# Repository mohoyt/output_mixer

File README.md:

# Output mixer for Eurorack

Inspired by the mixer in the Erica Synths x mki.edu line (but with added channels and SMD components)

## Features
- Eurorack format (3U panel height = 133.4mm)
- 8HP width (about 40mm)
- 4 inputs with pan (L-R) and level adjustable
- 2 outputs, line out and headphone out
- Mostly SMD with a couple through hole parts

## Issues
- [x] Pan is reversed
- [x] Not enough space for 1W 47R resistor
- [x] BD139/140 overheating

All addressed in current version (v1.1). The overheating was a result of poor quality BD139 and BD140 that I had sourced.

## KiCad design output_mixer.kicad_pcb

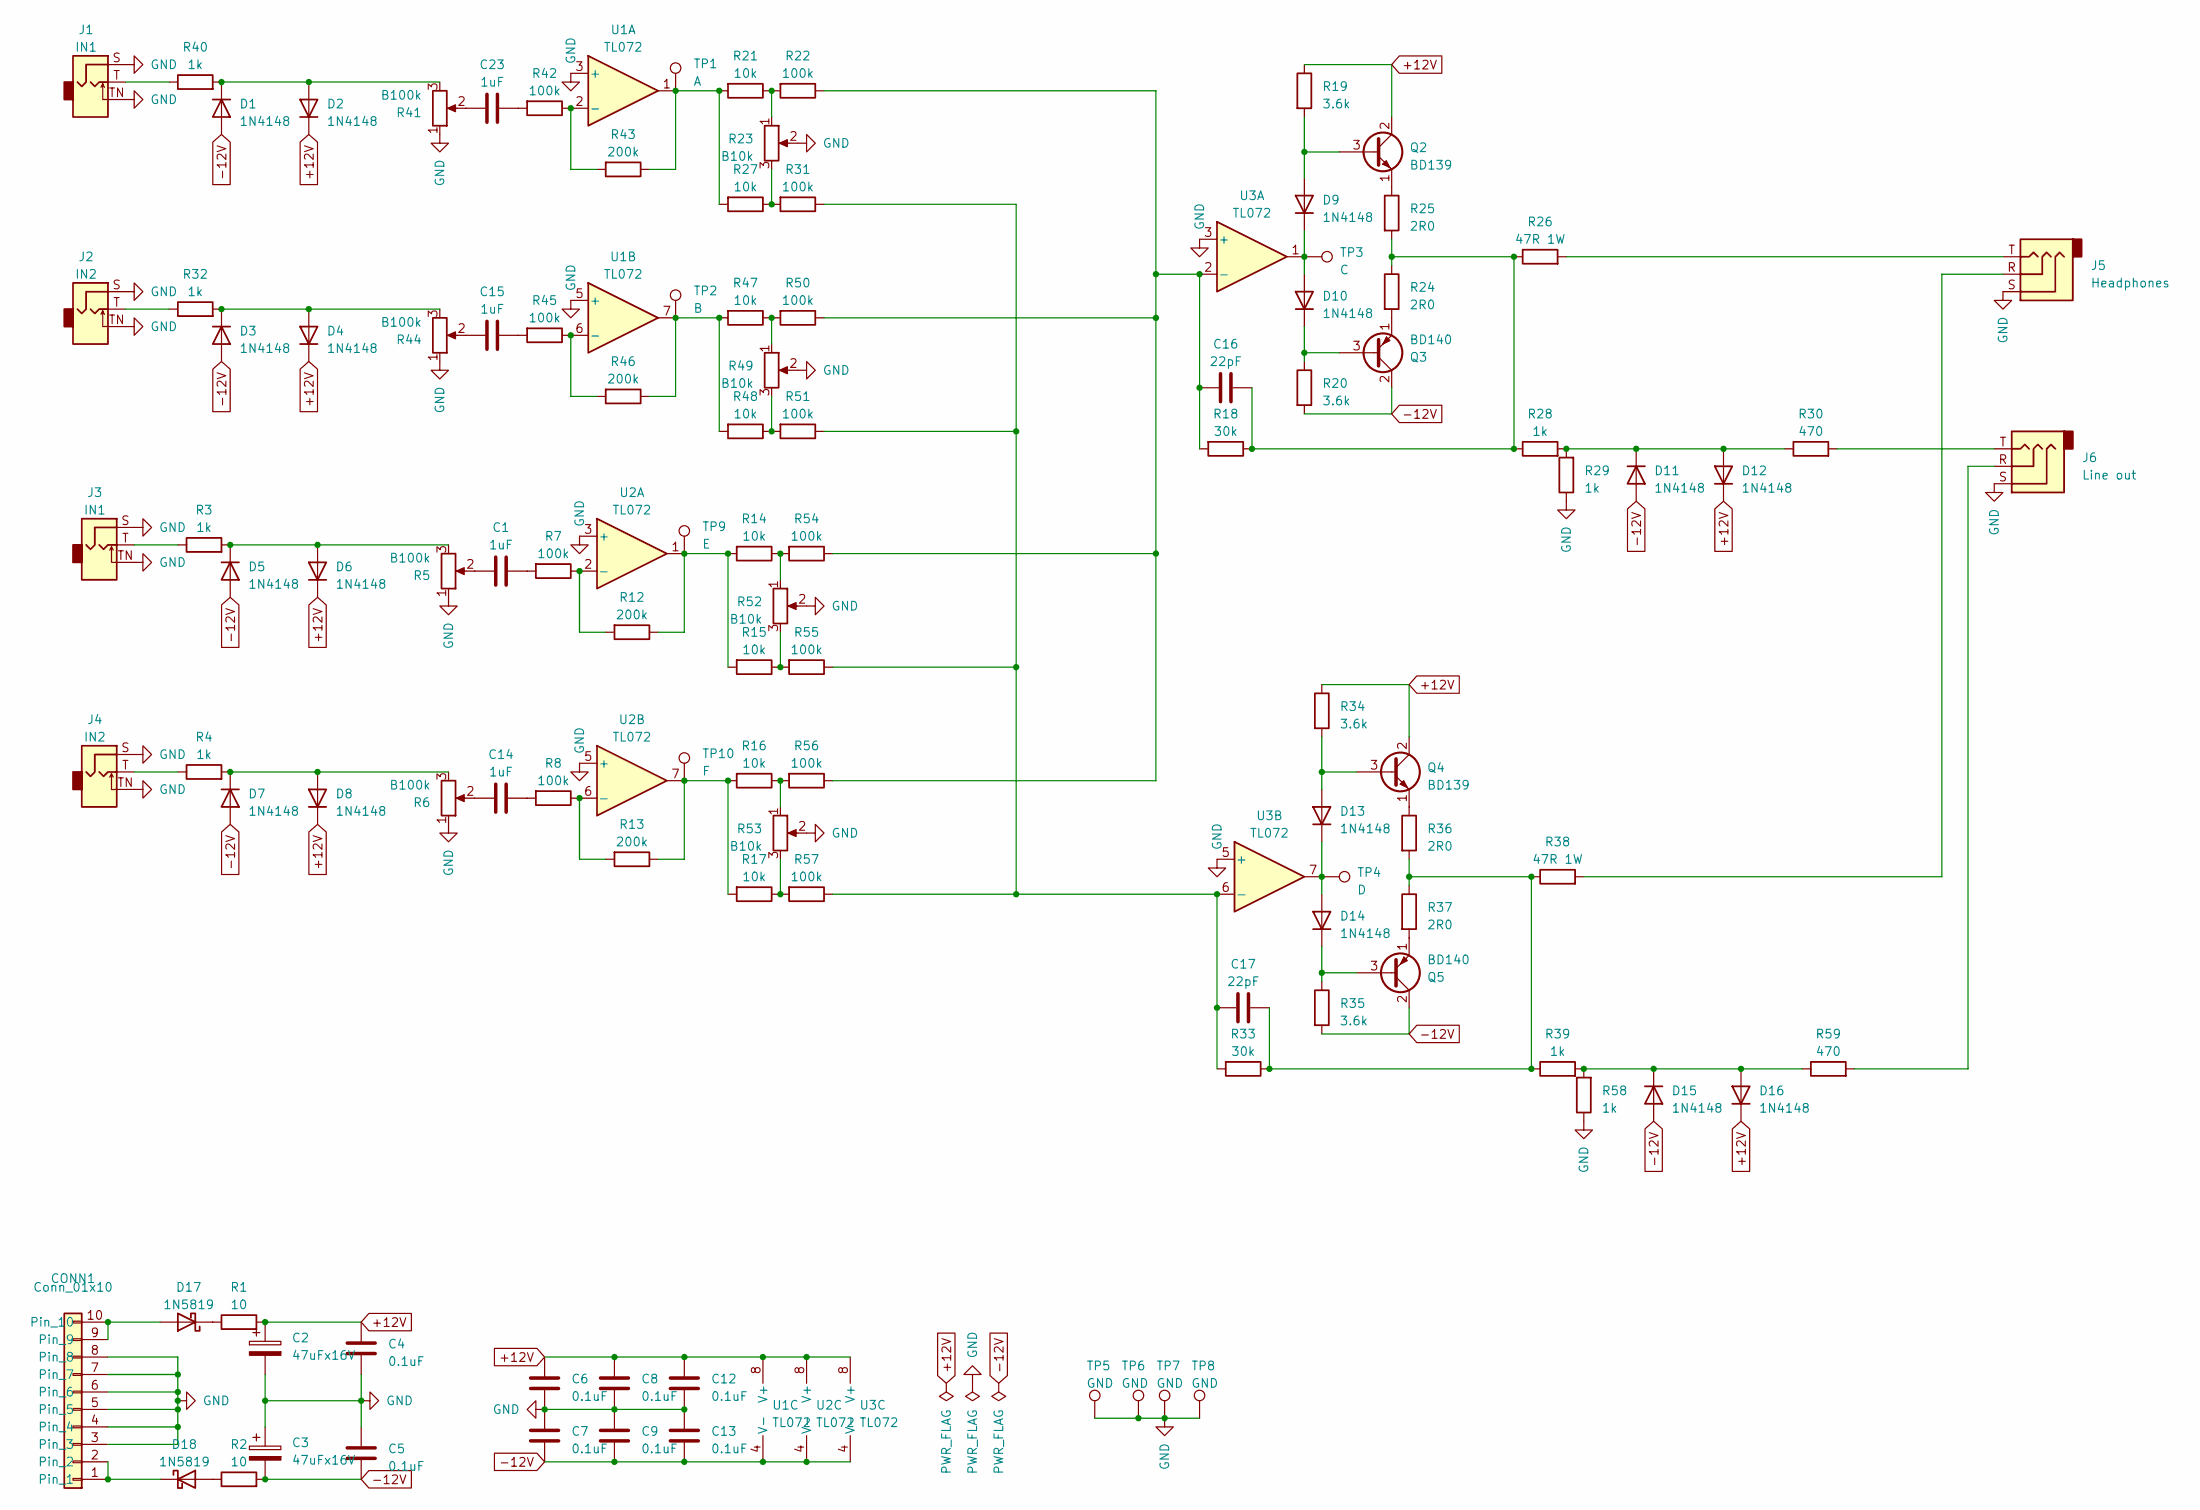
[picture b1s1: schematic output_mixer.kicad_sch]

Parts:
C1, C14, C15, C23: 1uF; C_0603_1608Metric; LCSC C15849
C2, C3: 47uFx16V; CP_Radial_D5.0mm_P2.50mm
C4, C5, C6, C7, C8, C9, C12, C13: 0.1uF; C_0603_1608Metric; LCSC C14663
C16, C17: 22pF; C_0603_1608Metric; LCSC C1653
CONN1: Conn_01x10; PinHeader_2x05_P2.54mm_Vertical_Shroud
D1, D2, D3, D4, D5, D6, D7, D8, D9, D10, D11, D12, D13, D14, D15, D16: 1N4148; D_SOD-123; LCSC C81598
D17, D18: 1N5819; D_SOD-323; LCSC C191023
J1, J3: IN1; Jack_3.5mm_QingPu_WQP-PJ398SM_Vertical_CircularHoles
J2, J4: IN2; Jack_3.5mm_QingPu_WQP-PJ398SM_Vertical_CircularHoles
J5: Headphones; Jack_3.5mm_Stereo_Unbranded
J6: Line out; Jack_3.5mm_Stereo_Unbranded
Q2, Q4: BD139; TO-126-3_Vertical
Q3, Q5: BD140; TO-126-3_Vertical
R1, R2: 10; R_Axial_DIN0207_L6.3mm_D2.5mm_P7.62mm_Horizontal
R3, R4, R28, R29, R32, R39, R40, R58: 1k; R_0805_2012Metric; LCSC C17513
R5, R6, R41, R44: B100k; Potentiometer_Alpha_RD901F-40-00D_Single_Vertical
R7, R8, R22, R31, R42, R45, R50, R51, R54, R55, R56, R57: 100k; R_0805_2012Metric; LCSC C149504
R12, R13, R43, R46: 200k; R_0805_2012Metric; LCSC C17539
R14, R15, R16, R17, R21, R27, R47, R48: 10k; R_0805_2012Metric; LCSC C17414
R18, R33: 30k; R_0805_2012Metric; LCSC C17621
R19, R20, R34, R35: 3.6k; R_0603_1608Metric; LCSC C22980
R23, R49, R52, R53: B10k; Potentiometer_Alpha_RD901F-40-00D_Single_Vertical
R24, R25, R36, R37: 2R0; R_Axial_DIN0207_L6.3mm_D2.5mm_P7.62mm_Horizontal
R26, R38: 47R 1W; R_Axial_DIN0309_L9.0mm_D3.2mm_P12.70mm_Horizontal
R30, R59: 470; R_0805_2012Metric; LCSC C17710
TP1: A; TestPoint_THTPad_D2.5mm_Drill1.2mm
TP2: B; TestPoint_THTPad_D2.5mm_Drill1.2mm
TP3: C; TestPoint_THTPad_D2.5mm_Drill1.2mm
TP4: D; TestPoint_THTPad_D2.5mm_Drill1.2mm
TP5, TP6, TP7, TP8: GND; TestPoint_THTPad_D2.5mm_Drill1.2mm
TP9: E; TestPoint_THTPad_D2.5mm_Drill1.2mm
TP10: F; TestPoint_THTPad_D2.5mm_Drill1.2mm
U1, U2, U3: TL072; SOP-8_3.9x4.9mm_P1.27mm; LCSC C6961

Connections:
+12V: C2.1, C4.1, C6.1, C8.1, C12.1, D2.1 (K), D4.1 (K), D6.1 (K), D8.1 (K), D12.1 (K), D16.1 (K), Q2.2 (C), Q4.2 (C), R1.2, R19.1, R34.1, U1.8 (V+), U2.8 (V+), U3.8 (V+)
-12V: C3.2, C5.2, C7.2, C9.2, C13.2, D1.2 (A), D3.2 (A), D5.2 (A), D7.2 (A), D11.2 (A), D15.2 (A), Q3.2 (C), Q5.2 (C), R2.2, R20.2, R35.2, U1.4 (V-), U2.4 (V-), U3.4 (V-)
GND: C2.2, C3.1, C4.2, C5.1, C6.2, C7.1, C8.2, C9.1, C12.2, C13.1, CONN1.3, CONN1.4, CONN1.5, CONN1.6, CONN1.7, CONN1.8, J1.S, J1.TN, J2.S, J2.TN, J3.S, J3.TN, J4.S, J4.TN, J5.S, J6.S, R5.1, R6.1, R23.2, R29.1, R41.1, R44.1, R49.2, R52.2, R53.2, R58.1, TP5.1, TP6.1, TP7.1, TP8.1, U1.3 (+), U1.5 (+), U2.3 (+), U2.5 (+), U3.3 (+), U3.5 (+)
unnamed: C1.1, R5.2
unnamed: C1.2, R7.2
unnamed: C14.1, R6.2
unnamed: C14.2, R8.2
unnamed: C15.1, R44.2
unnamed: C15.2, R45.2
unnamed: C16.2, R18.1, R24.1, R25.2, R26.1, R28.1
unnamed: C17.2, R33.1, R36.2, R37.1, R38.1, R39.1
unnamed: C23.1, R41.2
unnamed: C23.2, R42.2
unnamed: CONN1.1, CONN1.2, D18.1 (K)
unnamed: CONN1.9, CONN1.10, D17.2 (A)
unnamed: D1.1 (K), D2.2 (A), R40.2, R41.3
unnamed: D3.1 (K), D4.2 (A), R32.2, R44.3
unnamed: D5.1 (K), D6.2 (A), R3.2, R5.3
unnamed: D7.1 (K), D8.2 (A), R4.2, R6.3
unnamed: D9.2 (A), Q2.3 (B), R19.2
unnamed: D9.1 (K), D10.2 (A), TP3.1, U3.1
unnamed: D10.1 (K), Q3.3 (B), R20.1
unnamed: D11.1 (K), D12.2 (A), R28.2, R29.2, R30.1
unnamed: D13.2 (A), Q4.3 (B), R34.2
unnamed: D13.1 (K), D14.2 (A), TP4.1, U3.7
unnamed: D14.1 (K), Q5.3 (B), R35.1
unnamed: D15.1 (K), D16.2 (A), R39.2, R58.2, R59.1
unnamed: D17.1 (K), R1.1
unnamed: D18.2 (A), R2.1
unnamed: J1.T, R40.1
unnamed: J2.T, R32.1
unnamed: J3.T, R3.1
unnamed: J4.T, R4.1
unnamed: J5.R, R38.2
unnamed: J5.T, R26.2
unnamed: J6.R, R59.2
unnamed: J6.T, R30.2
unnamed: Q2.1 (E), R25.1
unnamed: Q3.1 (E), R24.2
unnamed: Q4.1 (E), R36.1
unnamed: Q5.1 (E), R37.2
unnamed: R12.1, R14.2, R15.2, TP9.1, U2.1
unnamed: R13.1, R16.2, R17.2, TP10.1, U2.7
unnamed: R14.1, R52.1, R54.2
unnamed: R15.1, R52.3, R55.2
unnamed: R16.1, R53.1, R56.2
unnamed: R17.1, R53.3, R57.2
unnamed: R21.1, R22.2, R23.1
unnamed: R21.2, R27.2, R43.1, TP1.1, U1.1
unnamed: R23.3, R27.1, R31.2
unnamed: R46.1, R47.2, R48.2, TP2.1, U1.7
unnamed: R47.1, R49.1, R50.2
unnamed: R48.1, R49.3, R51.2
unnamed: R42.1, R43.2, U1.2 (-)
unnamed: R45.1, R46.2, U1.6 (-)
unnamed: R7.1, R12.2, U2.2 (-)
unnamed: R8.1, R13.2, U2.6 (-)
unnamed: C16.1, R18.2, R22.1, R50.1, R54.1, R56.1, U3.2 (-)
unnamed: C17.1, R31.1, R33.2, R51.1, R55.1, R57.1, U3.6 (-)

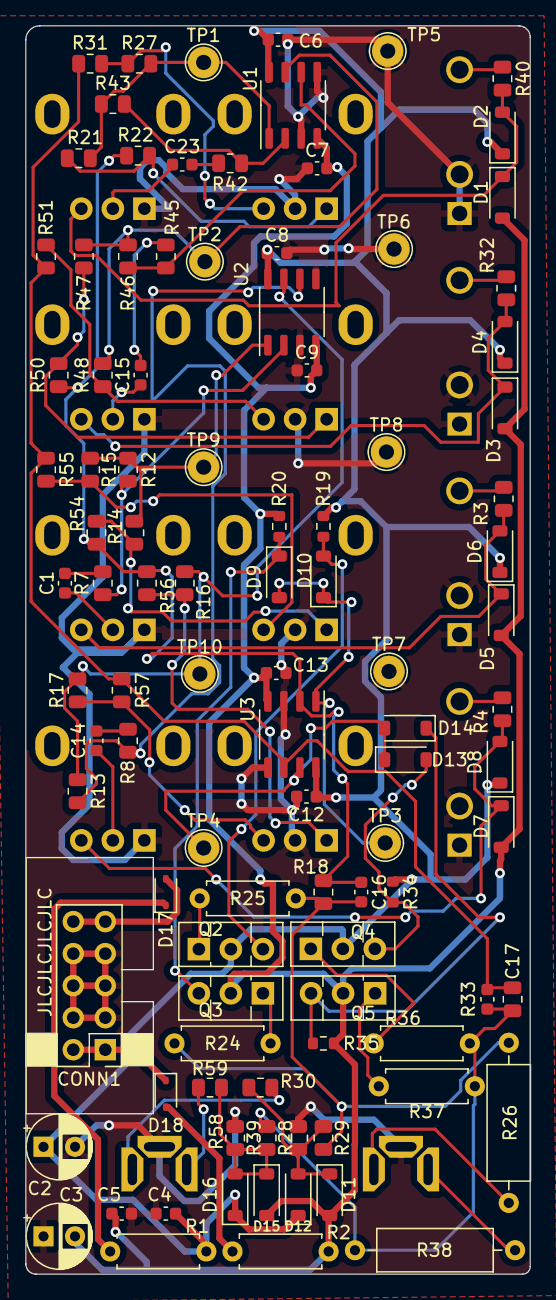
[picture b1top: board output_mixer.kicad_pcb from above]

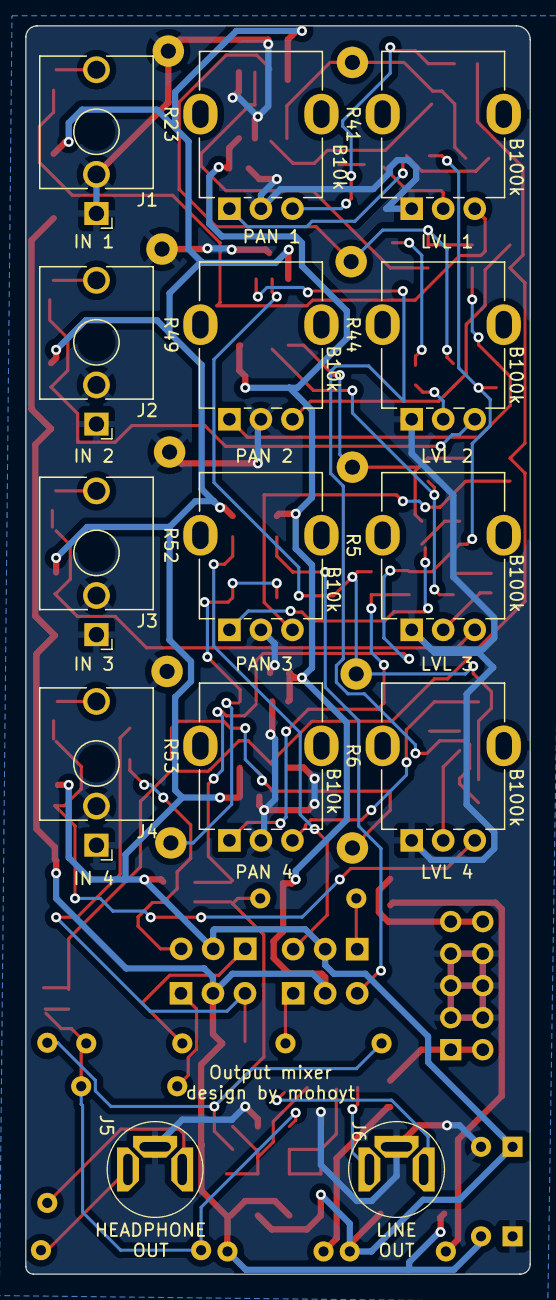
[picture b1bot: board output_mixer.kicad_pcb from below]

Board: 2 copper layers, 40.0 x 99.0 mm, 114 parts (14 on the bottom side), 59 nets.

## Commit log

2023-11-20 Schematic done
2023-11-21 schematic done, some parts added to PCB
2023-12-08 Design done and sent to production
2024-01-05 BOM added
2024-01-05 v1 issues fixed (opposite panning and 47R resistor footprint size)
2024-04-30 Readme updated with photos
2024-04-30 Schematic and license added
2024-05-17 Readme updated and panel image added
2025-03-09 Added panel stl
